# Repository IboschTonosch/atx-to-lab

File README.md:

# atx-to-lab

You need the following tools to view or edit the files
* [KiCAD](https://kicad.org) - Edit PCB and Schematic files (.pro, .pcb, .sch).
* [FreeCAD](https://freecadweb.org) - Edit Assembly CAD Files.

Optional tools
* [Inkscape](https://inkscape.org) - Inkscape is a free and open-source vector graphics editor.

## Section Title
> What is this all about.

Complete design to turn an PC atx power supply into a constant current lab power supply

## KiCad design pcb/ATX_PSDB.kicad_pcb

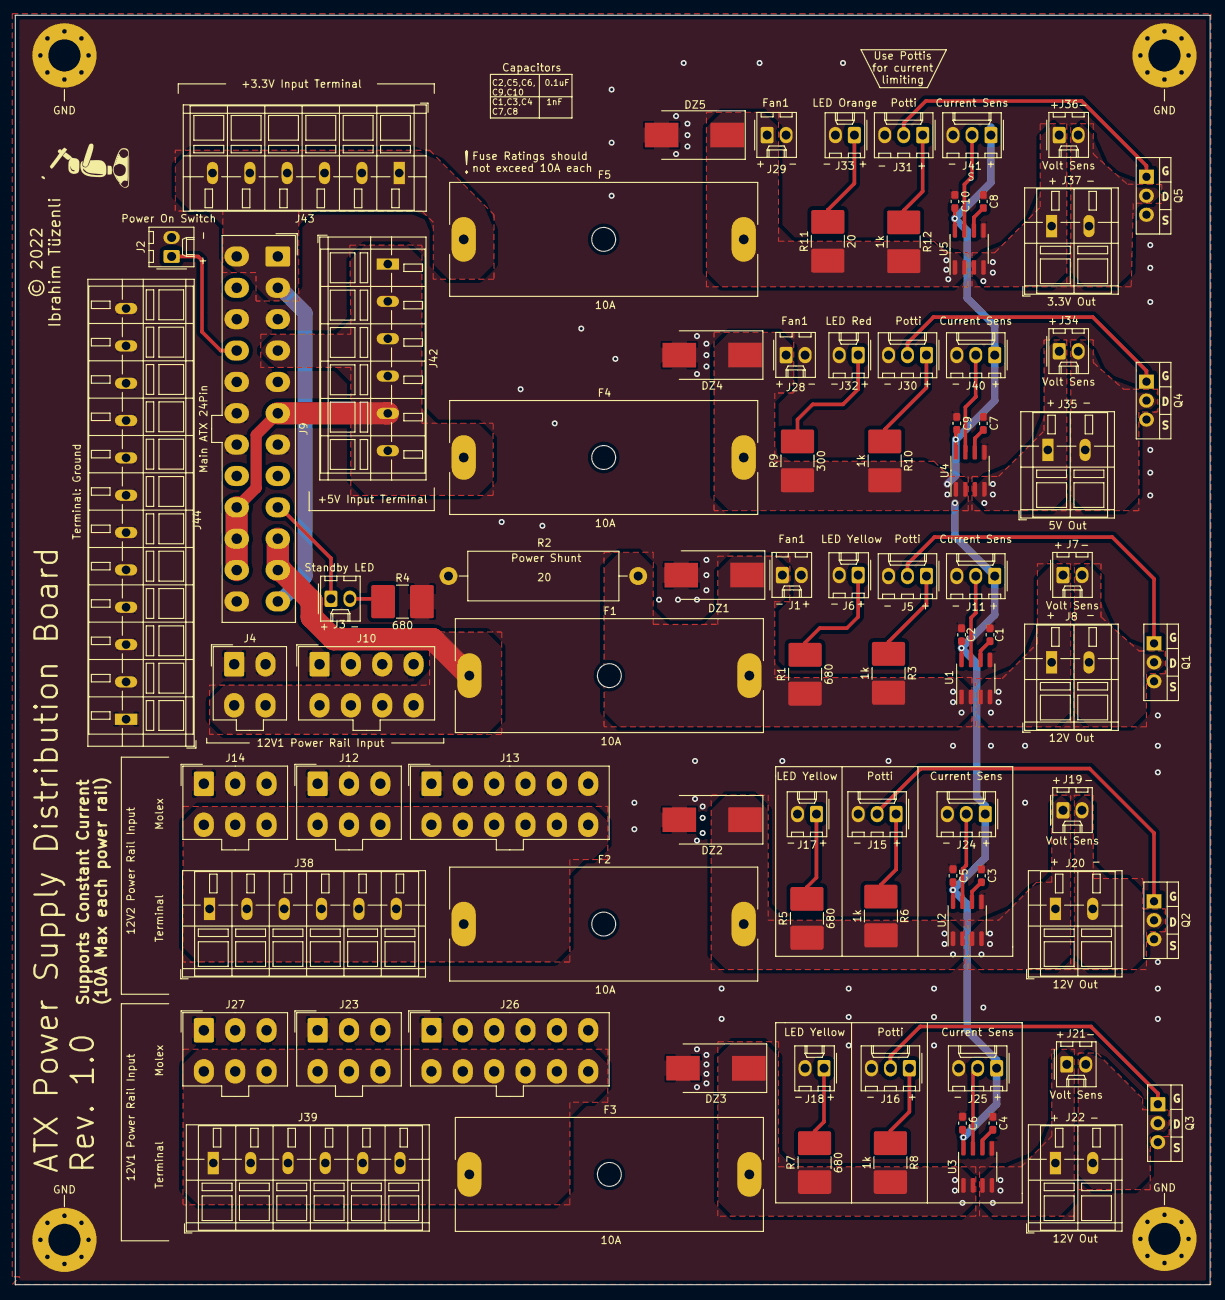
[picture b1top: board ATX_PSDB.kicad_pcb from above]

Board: 2 copper layers, 160.0 x 170.0 mm, 86 parts (0 on the bottom side), 49 nets.

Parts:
C1, C3, C4, C7, C8: 1nF; C_0603_1608Metric_Pad1.05x0.95mm_HandSolder
C2, C5, C6, C9, C10: 0.1uF; C_0603_1608Metric_Pad1.05x0.95mm_HandSolder
DZ1, DZ2, DZ3, DZ4, DZ5: D_Zener_ALT; D_SMC_Handsoldering
F1, F2, F3, F4, F5: 10A; Fuseholder_Cylinder-6.3x32mm_Schurter_0031-8002_Horizontal_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
J1, J28, J29: Fan1; Molex_KK-254_AE-6410-02A_1x02_P2.54mm_Vertical
J2: Power On Switch; Molex_KK-254_AE-6410-02A_1x02_P2.54mm_Vertical
J3: Standby LED; Molex_KK-254_AE-6410-02A_1x02_P2.54mm_Vertical
J4: ATX 12V1 Input; Molex_Mini-Fit_Jr_5566-04A_2x02_P4.20mm_Vertical
J5, J15, J16, J30, J31: Potti; Molex_KK-254_AE-6410-03A_1x03_P2.54mm_Vertical
J6, J17, J18: LED Yellow; Molex_KK-254_AE-6410-02A_1x02_P2.54mm_Vertical
J7, J19, J21, J34, J36: Volt Sens; Molex_KK-254_AE-6410-02A_1x02_P2.54mm_Vertical
J8, J20, J22: 12V Out; TerminalBlock_WAGO_236-102_1x02_P5.00mm_45Degree
J9: Main ATX 24Pin; Molex_Mini-Fit_Jr_5566-24A_2x12_P4.20mm_Vertical
J10: ATX 12V1 Input; Molex_Mini-Fit_Jr_5566-08A_2x04_P4.20mm_Vertical
J11, J24, J25, J40, J41: Current Sens; Molex_KK-254_AE-6410-03A_1x03_P2.54mm_Vertical
J12, J14: Molex: ATX 12V2 Input; Molex_Mini-Fit_Jr_5566-06A_2x03_P4.20mm_Vertical
J13: Molex: ATX 12V2 Input; Molex_Mini-Fit_Jr_5566-12A_2x06_P4.20mm_Vertical
J23, J27: Molex: ATX 12V3 Input; Molex_Mini-Fit_Jr_5566-06A_2x03_P4.20mm_Vertical
J26: Molex: ATX 12V3 Input; Molex_Mini-Fit_Jr_5566-12A_2x06_P4.20mm_Vertical
J32: LED Red; Molex_KK-254_AE-6410-02A_1x02_P2.54mm_Vertical
J33: LED Orange; Molex_KK-254_AE-6410-02A_1x02_P2.54mm_Vertical
J35: 5V Out; TerminalBlock_WAGO_236-102_1x02_P5.00mm_45Degree
J37: 3.3V Out; TerminalBlock_WAGO_236-102_1x02_P5.00mm_45Degree
J38: Terminal: +12V2 Input; TerminalBlock_WAGO_236-106_1x06_P5.00mm_45Degree
J39: Terminal: +12V3 Input; TerminalBlock_WAGO_236-106_1x06_P5.00mm_45Degree
J42: Terminal: +5V Input; TerminalBlock_WAGO_236-106_1x06_P5.00mm_45Degree
J43: Terminal: +3.3V Input; TerminalBlock_WAGO_236-106_1x06_P5.00mm_45Degree
J44: Terminal: Ground; TerminalBlock_WAGO_236-112_1x12_P5.00mm_45Degree
Q1, Q2, Q3, Q4, Q5: Q_NMOS_DGS; TO-220-3_Vertical
R1, R4, R5, R7: 680; R_2816_7142Metric_Pad3.20x4.45mm_HandSolder
R2: 20; R_Axial_Power_L20.0mm_W6.4mm_P25.40mm
R3, R6, R8, R10, R12: 1k; R_2816_7142Metric_Pad3.20x4.45mm_HandSolder
R9: 300; R_2816_7142Metric_Pad3.20x4.45mm_HandSolder
R11: 20; R_2816_7142Metric_Pad3.20x4.45mm_HandSolder
U1, U2, U3, U4, U5: ACS712xLCTR-20A; SOIC-8_3.9x4.9mm_P1.27mm

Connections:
3.3V-: J36.2, J37.2, Q5.2
5V-: J34.2, J35.2, Q4.2
12V1-: J7.2, J8.2, Q1.2
12V2-: J19.2, J20.2, Q2.2
12V3-: J21.2, J22.2, Q3.2
+3.3V: F5.1, J9.1, J9.2, J9.12, J9.13, J43.1, J43.2, J43.3, J43.4, J43.5, J43.6
+5V: F4.1, J9.4, J9.6, J9.21, J9.22, J9.23, J42.1, J42.2, J42.3, J42.4, J42.5, J42.6
+5VSB: J3.1, J9.9
+12V1: F1.1, J4.3, J4.4, J9.10, J9.11, J10.5, J10.6, J10.7, J10.8
+12V2: F2.1, J12.4, J12.5, J12.6, J13.7, J13.8, J13.9, J13.10, J13.11, J13.12, J14.4, J14.5, J14.6, J38.1, J38.2, J38.3, J38.4, J38.5, J38.6
+12V3: F3.1, J23.4, J23.5, J23.6, J26.7, J26.8, J26.9, J26.10, J26.11, J26.12, J27.4, J27.5, J27.6, J39.1, J39.2, J39.3, J39.4, J39.5, J39.6
+F5V: C2.2, C5.2, C6.2, C9.2, C10.2, DZ4.1, F4.2, J11.1, J24.1, J25.1, J28.1, J40.1, J41.1, R9.1, R10.2, U1.8, U2.8, U3.8, U4.1, U4.2, U4.8, U5.8
GND: C1.1, C2.1, C3.1, C4.1, C5.1, C6.1, C7.1, C8.1, C9.1, C10.1, DZ1.2, DZ2.2, DZ3.2, DZ4.2, DZ5.2, J1.2, J2.2, J4.1, J4.2, J5.3, J6.2, J9.3, J9.5, J9.7, J9.15, J9.17, J9.18, J9.19, J9.24, J10.1, J10.2, J10.3, J10.4, J11.3, J12.1, J12.2, J12.3, J13.1, J13.2, J13.3, J13.4, J13.5, J13.6, J14.1, J14.2, J14.3, J15.3, J16.3, J17.2, J18.2, J23.1, J23.2, J23.3, J24.3, J25.3, J26.1, J26.2, J26.3, J26.4, J26.5, J26.6, J27.1, J27.2, J27.3, J28.2, J29.2, J30.3, J31.3, J32.2, J33.2, J40.3, J41.3, J44.1, J44.2, J44.3, J44.4, J44.5, J44.6, J44.7, J44.8, J44.9, J44.10, J44.11, J44.12, Q1.3, Q2.3, Q3.3, Q4.3, Q5.3, R2.2, R4.2, U1.5, U2.5, U3.5, U4.5, U5.5
unnamed: C1.2, U1.6
unnamed: C3.2, U2.6
unnamed: C4.2, U3.6
unnamed: C7.2, U4.6
unnamed: C8.2, U5.6
unnamed: DZ1.1, F1.2, J1.1, R1.1, R2.1, R3.2, U1.1, U1.2
unnamed: DZ2.1, F2.2, R5.1, R6.2, U2.1, U2.2
unnamed: DZ3.1, F3.2, R7.1, R8.2, U3.1, U3.2
unnamed: DZ5.1, F5.2, J29.1, R11.1, R12.2, U5.1, U5.2
unnamed: J3.2, R4.1
unnamed: J5.1, R3.1
unnamed: J5.2, Q1.1
unnamed: J6.1, R1.2
unnamed: J7.1, J8.1, U1.3, U1.4
unnamed: J11.2, U1.7
unnamed: J15.1, R6.1
unnamed: J15.2, Q2.1
unnamed: J16.1, R8.1
unnamed: J16.2, Q3.1
unnamed: J17.1, R5.2
unnamed: J18.1, R7.2
unnamed: J19.1, J20.1, U2.3, U2.4
unnamed: J21.1, J22.1, U3.3, U3.4
unnamed: J24.2, U2.7
unnamed: J25.2, U3.7
unnamed: J30.1, R10.1
unnamed: J30.2, Q4.1
unnamed: J31.1, R12.1
unnamed: J31.2, Q5.1
unnamed: J32.1, R9.2
unnamed: J33.1, R11.2
unnamed: J34.1, J35.1, U4.3, U4.4
unnamed: J36.1, J37.1, U5.3, U5.4
unnamed: J40.2, U4.7
unnamed: J41.2, U5.7
PS_ON: J2.1, J9.16

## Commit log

2020-06-20 Adding gitignore for kicad project
2020-06-20 changing gitignore place
2020-06-20 Adding KiCad project
2021-10-07 protection changes
2022-01-15 moved all sub schematics to base schematic sheet due to minor complexity
2022-02-13 Redesign
2022-02-13 labeling
2022-02-27 blub
2022-02-27 Finalizing and labeling schematics
2022-02-28 Annotated schematic symbols
2022-02-28 performed rule check
2022-02-28 Assigned pcb footprints
2022-03-09 some cleanup
2022-03-12 changed terminal blocks to wago footprints
2022-03-13 More pcb layout
2022-03-17 densified circuit, defined edge cut, added mounting holes
2022-03-18 Adding Traces
2022-03-18 More traces
2022-03-18 cleanup
2022-03-19 refit traces, added global label added text
2022-03-19 Corrections and so on
2022-03-20 finalization Rev. 1.0
2022-03-21 Added Trademark, cleanup and so on
2022-03-21 Schematic corrections and new netlist generated
2022-03-23 redesigned logo
2022-03-23 correction
2022-03-26 Changed File Structure
2022-03-26 edit gitignore
2022-03-26 renaming files, editing readme
2022-03-27 edit readme
2022-04-06 changed filename
2022-04-06 Migrate to KiCad 6.0
2022-05-09 Starting Frame Design
2022-05-14 baseplate sketch
2022-05-22 housing base fillets
2022-05-22 added inner increasing of the base plane
2022-05-22 created final base pad
2022-05-22 startet housing
2022-05-22 giving more structure
2022-05-22 finished frame and provided stl files
2022-05-28 changed frame style slightly
2022-05-28 designed top frame
2022-05-28 frame top done
2022-05-28 sketching front panel
2022-05-28 Front Panel finished
2022-05-28 added screw holes
2022-05-29 resized side panel
2022-08-18 added atx base stand
2022-08-18 base atx stand

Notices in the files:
pcb/ATX_PSDB.kicad_pcb:
© 2022
